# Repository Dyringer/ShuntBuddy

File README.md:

# ShuntBuddy ⚡

<table>
  <tr>
    <td>  </td>
  </tr>
</table>

**ShuntBuddy** is an active oscilloscope adapter designed for precise current measurement. It eliminates the hassle of measuring high-side current by converting the voltage drop across a shunt resistor into a buffered, amplified signal that your oscilloscope can easily display.

## How it Works

ShuntBuddy sits between your power supply and your load. It uses the **Texas Instruments INA225**—a fully integrated, programmable gain difference amplifier. The device captures the tiny voltage drop across an internal 10mΩ shunt and scales it up.

Simply connect ShuntBuddy to your scope via a BNC cable, power it via USB-C, and your current readings appear as a voltage signal.

---

---

## Technical Specifications

* **Amplifier:** INA225 (High-precision, integrated gain resistors)
* **Input Shunt:** 10mΩ 
* **Power Input:** USB-C (5V)
* **Output:** BNC (Compatible with all standard oscilloscopes)
* **Form Factor:** Current-to-Voltage Probe (acts like a x10 probe)

### Gain & Current Ranges

With the onboard **10mΩ shunt**, the following ranges are available via the DIP switch:

| Setting | Gain () | Scale Factor | Max Current (at 4V Output) |
| --- | --- | --- | --- |
| **G1** | 25 | 250 mV/A | **16.0 A** |
| **G2** | 50 | 500 mV/A | **8.0 A** |
| **G3** | 100 | 1 V/A | **4.0 A** |
| **G4** | 200 | 2 V/A | **2.0 A** |

---

## Configuration

### 1. Gain Selection (DIP Switch)

The INA225 allows you to hardware-configure the gain. This is useful for "zooming in" on low-power signals (G4) or measuring high-current surges (G1) without clipping the output.

### 2. Reference Voltage ()

You can shift the "zero" point of your measurement to handle different scenarios:

* **4V Reference:** Optimized for **Unidirectional** measurement (Current flowing from Source to Load). Provides the widest dynamic range for power consumption analysis.
* **2V Reference:** Optimized for **Bidirectional** measurement. This centers the zero point, allowing you to see both charging and discharging currents (positive and negative swings).

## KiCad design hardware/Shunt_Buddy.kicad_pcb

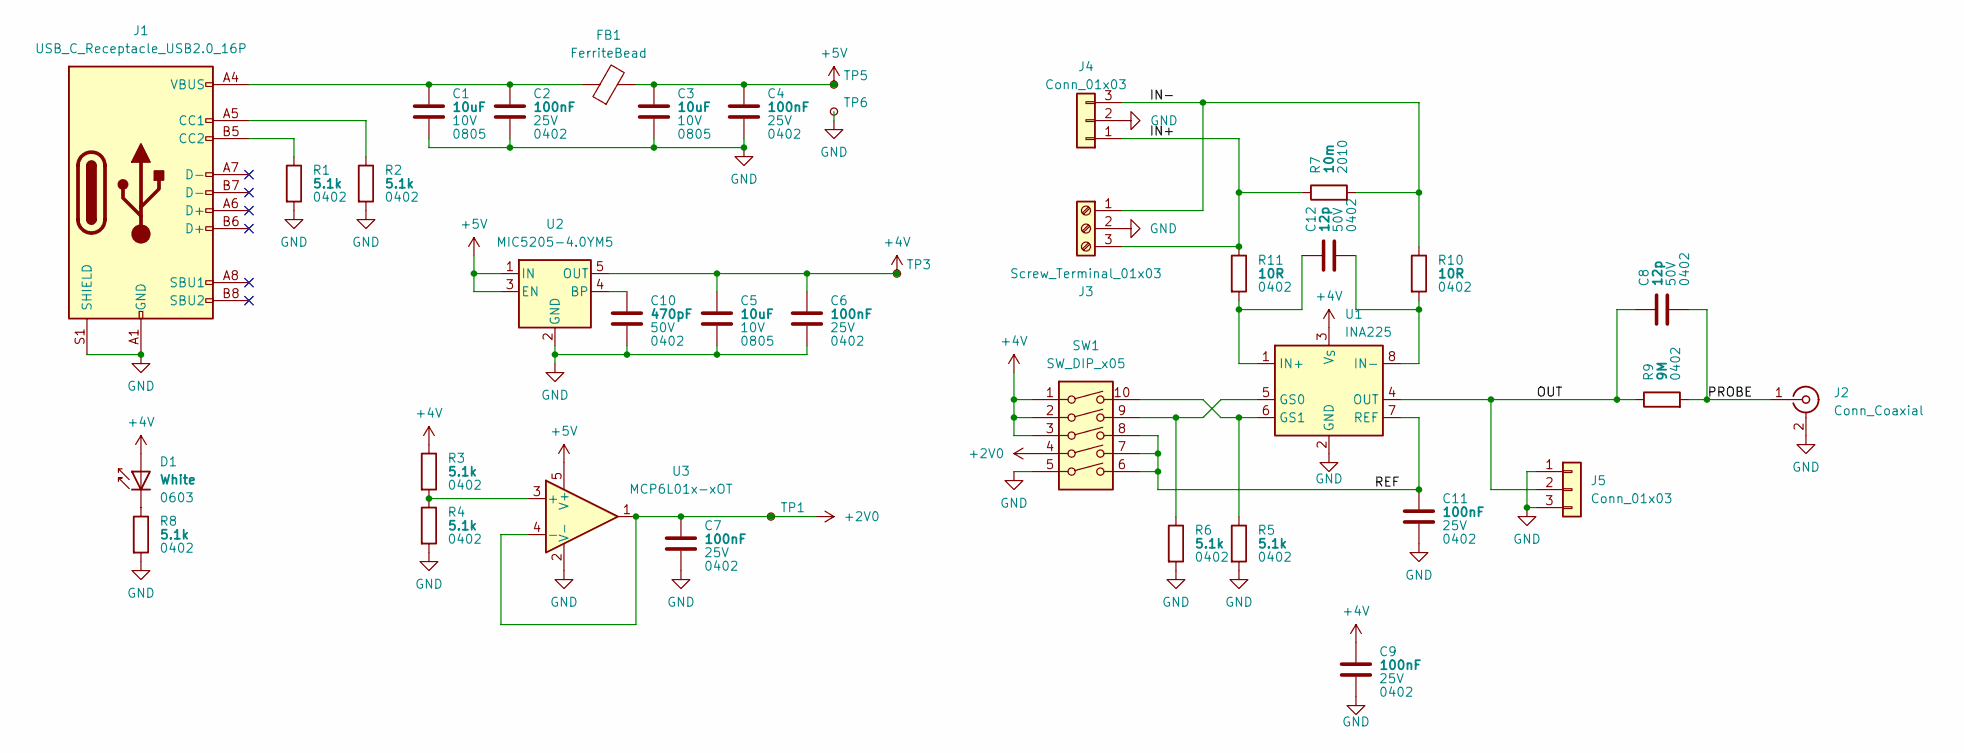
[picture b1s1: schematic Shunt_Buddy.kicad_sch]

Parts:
C1, C3, C5: 10uF; C_0805_2012Metric; Voltage 10V
C2, C4, C6, C7, C9, C11: 100nF; C_0402_1005Metric; Voltage 25V
C8, C12: 12p; C_0402_1005Metric; Voltage 50V
C10: 470pF; C_0402_1005Metric; Voltage 50V
D1: White; LED_0603_1608Metric
FB1: FerriteBead; L_0603_1608Metric
J1: USB_C_Receptacle_USB2.0_16P; USB_C_Receptacle_GCT_USB4110
J2: Conn_Coaxial; BNC_Amphenol_B6252HB-NPP3G-50_Horizontal
J3: Screw_Terminal_01x03; TerminalBlock_Degson_DG250-3.5-03P_1x03_P3.50mm_45Degree
J4, J5: Conn_01x03; PinHeader_1x03_P2.54mm_Horizontal
R1, R2, R3, R4, R5, R6, R8: 5.1k; R_0402_1005Metric
R7: 10m; R_2010_5025Metric
R9: 9M; R_0402_1005Metric
R10, R11: 10R; R_0402_1005Metric
SW1: SW_DIP_x05; SW_DIP_SPSTx05_Slide_6.7x14.26mm_W6.73mm_P2.54mm_LowProfile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
TP1, TP3, TP5, TP6: TestPoint_Small; TestPoint_Pad_D1.0mm
U1: INA225; VSSOP-8_3x3mm_P0.65mm
U2: MIC5205-4.0YM5; SOT-23-5
U3: MCP6L01x-xOT; SOT-23-5

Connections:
+2V0: C7.1, SW1.4, TP1.1 (1_1), U3.1, U3.4 (-)
+4V: C5.1, C6.1, C9.1, D1.2 (A), R3.1, SW1.1, SW1.2, SW1.3, TP3.1 (1_1), U1.3 (V_{S}), U2.5 (OUT)
+5V: C3.1, C4.1, FB1.2, TP5.1 (1_1), U2.1 (IN), U2.3 (EN), U3.5 (V+)
/IN+: J3.3, J4.1, R7.1, R11.1
/IN-: J3.1, J4.3, R7.2, R10.1
/OUT: C8.1, J5.2, R9.1, U1.4 (OUT)
/PROBE: C8.2, J2.1 (In), R9.2
/REF: C11.1, SW1.6, SW1.7, SW1.8, U1.7 (REF)
GND: C1.2, C2.2, C3.2, C4.2, C5.2, C6.2, C7.2, C9.2, C10.2, C11.2, J1.A1 (GND), J1.A12 (GND), J1.B1 (GND), J1.B12 (GND), J1.S1 (SHIELD), J2.2 (Ext), J3.2, J4.2, J5.1, J5.3, R1.2, R2.2, R4.2, R5.2, R6.2, R8.2, SW1.5, TP6.1 (1_1), U1.2 (GND), U2.2 (GND), U3.2 (V-)
unnamed: C1.1, C2.1, FB1.1, J1.A4 (VBUS), J1.A9 (VBUS), J1.B4 (VBUS), J1.B9 (VBUS)
unnamed: D1.1 (K), R8.1
unnamed: J1.A5 (CC1), R2.1
unnamed: J1.B5 (CC2), R1.1
unnamed: R6.1, SW1.9, U1.5 (GS0)
unnamed: R5.1, SW1.10, U1.6 (GS1)
unnamed: C12.1, R11.2, U1.1 (IN+)
unnamed: C12.2, R10.2, U1.8 (IN-)
unnamed: C10.1, U2.4 (BP)
unnamed: R3.2, R4.1, U3.3 (+)

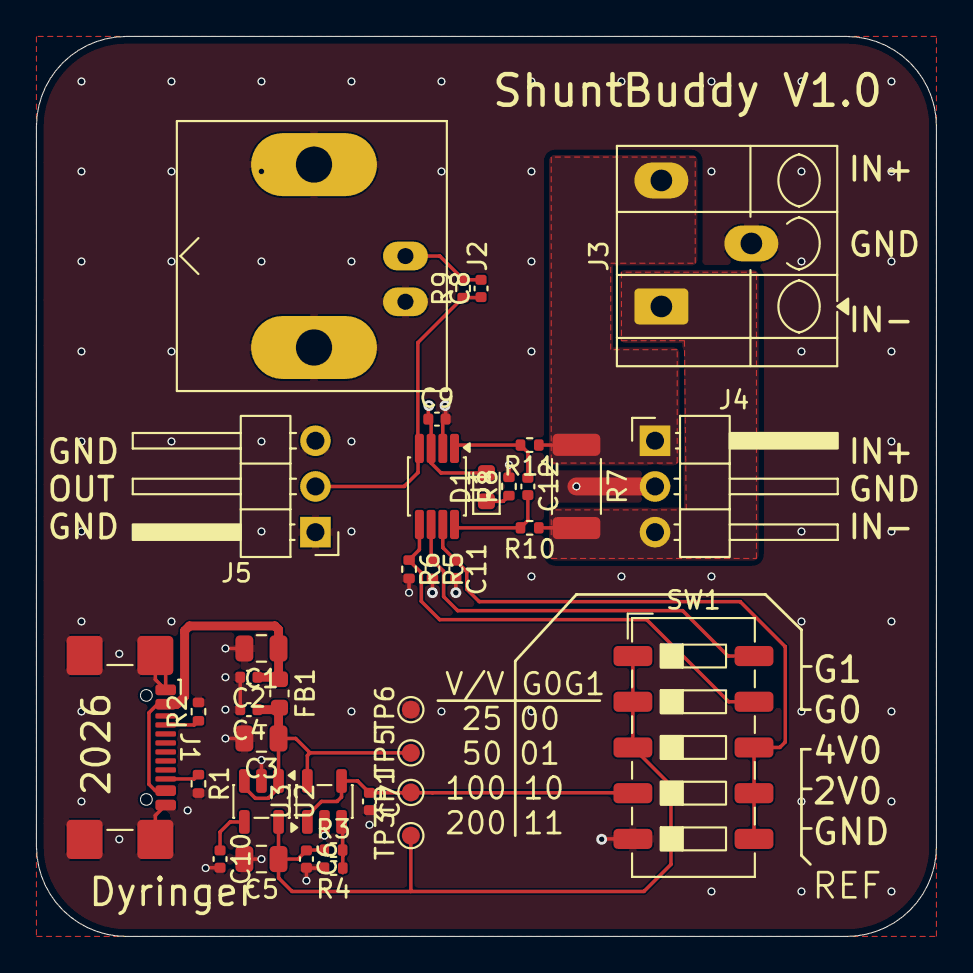
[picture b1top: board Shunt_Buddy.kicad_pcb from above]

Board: 2 copper layers, 50.0 x 50.0 mm, 38 parts (0 on the bottom side), 19 nets.

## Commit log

2026-02-03 Added all files
2026-02-03 Removed lock files
2026-02-03 Updated gitignore to skip lock files
2026-02-07 Cleanups
